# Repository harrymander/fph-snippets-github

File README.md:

# Code samples

1. `recap-instrumentation`: Research data collection device.

   C project for Atmel (Microchip) ATSAM4S16B using Freertos. Modules of
   interest:

   * `recap-instrumentation/sw/src/sensors.c`: sensor reading in timer ISR.
   * `recap-instrumentation/sw/drivers/twi-async/twi-async.c`: interrupt-driven
     'asynchronous' I2C read.

2. `recap-usb-reader`: Host application for the device above.

   Cross-platform C++ project for realtime data acquisition and visualisation.
   Uses Dear ImGui immediate mode GUI framework. GUI and application logic run
   from the event loop of graphics framework (DirectX on Windows, GLFW on
   Linux).

   Modules of interest:

   * `recap-usb-reader/gui/src/device.hpp`: boundary between the device library
     and the GUI. State pattern.
   * `recap-usb-reader/gui/src/observable.hpp`: observer pattern used to
     decouple the device layer from the GUI views.
   * `recap-usb-reader/lib/usb-reader/include/recap/usb-reader/reader.hpp`:
     device library interface.

3. `swallow-labeller`: Tool for annotating recordings from the device.
   (`complete-swallow-labelling` branch).

   C++, Dear ImGui. Modules of interest:

   * `swallow-labeller/src/gui/task-filter.cpp`: defining filters for different
     items in GUI list. Example of runtime polymorphism.
   * `swallow-labeller/src/gui/task-view.cpp`, lines 203-346: undo/redo using
     the command pattern.

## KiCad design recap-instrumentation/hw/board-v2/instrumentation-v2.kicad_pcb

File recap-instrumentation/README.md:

RECAP Instrumentation
=====================

Data collection device for the RECAP project. This is a reimplementation of the
original data collection prototype that was implemented using a Raspberry Pi.
This implementation is based around a Atmel SAM4S microcontroller connected to
the following sensors:

 - An ADC for audio recording
 - Air flow meter
 - Differential pressure sensor
 - H2S gas sensor

The data is continuously measured by the device and streamed over a USB CDC
interface using a custom data format. See [`sw/README.md`](sw/README.md) for
more information.

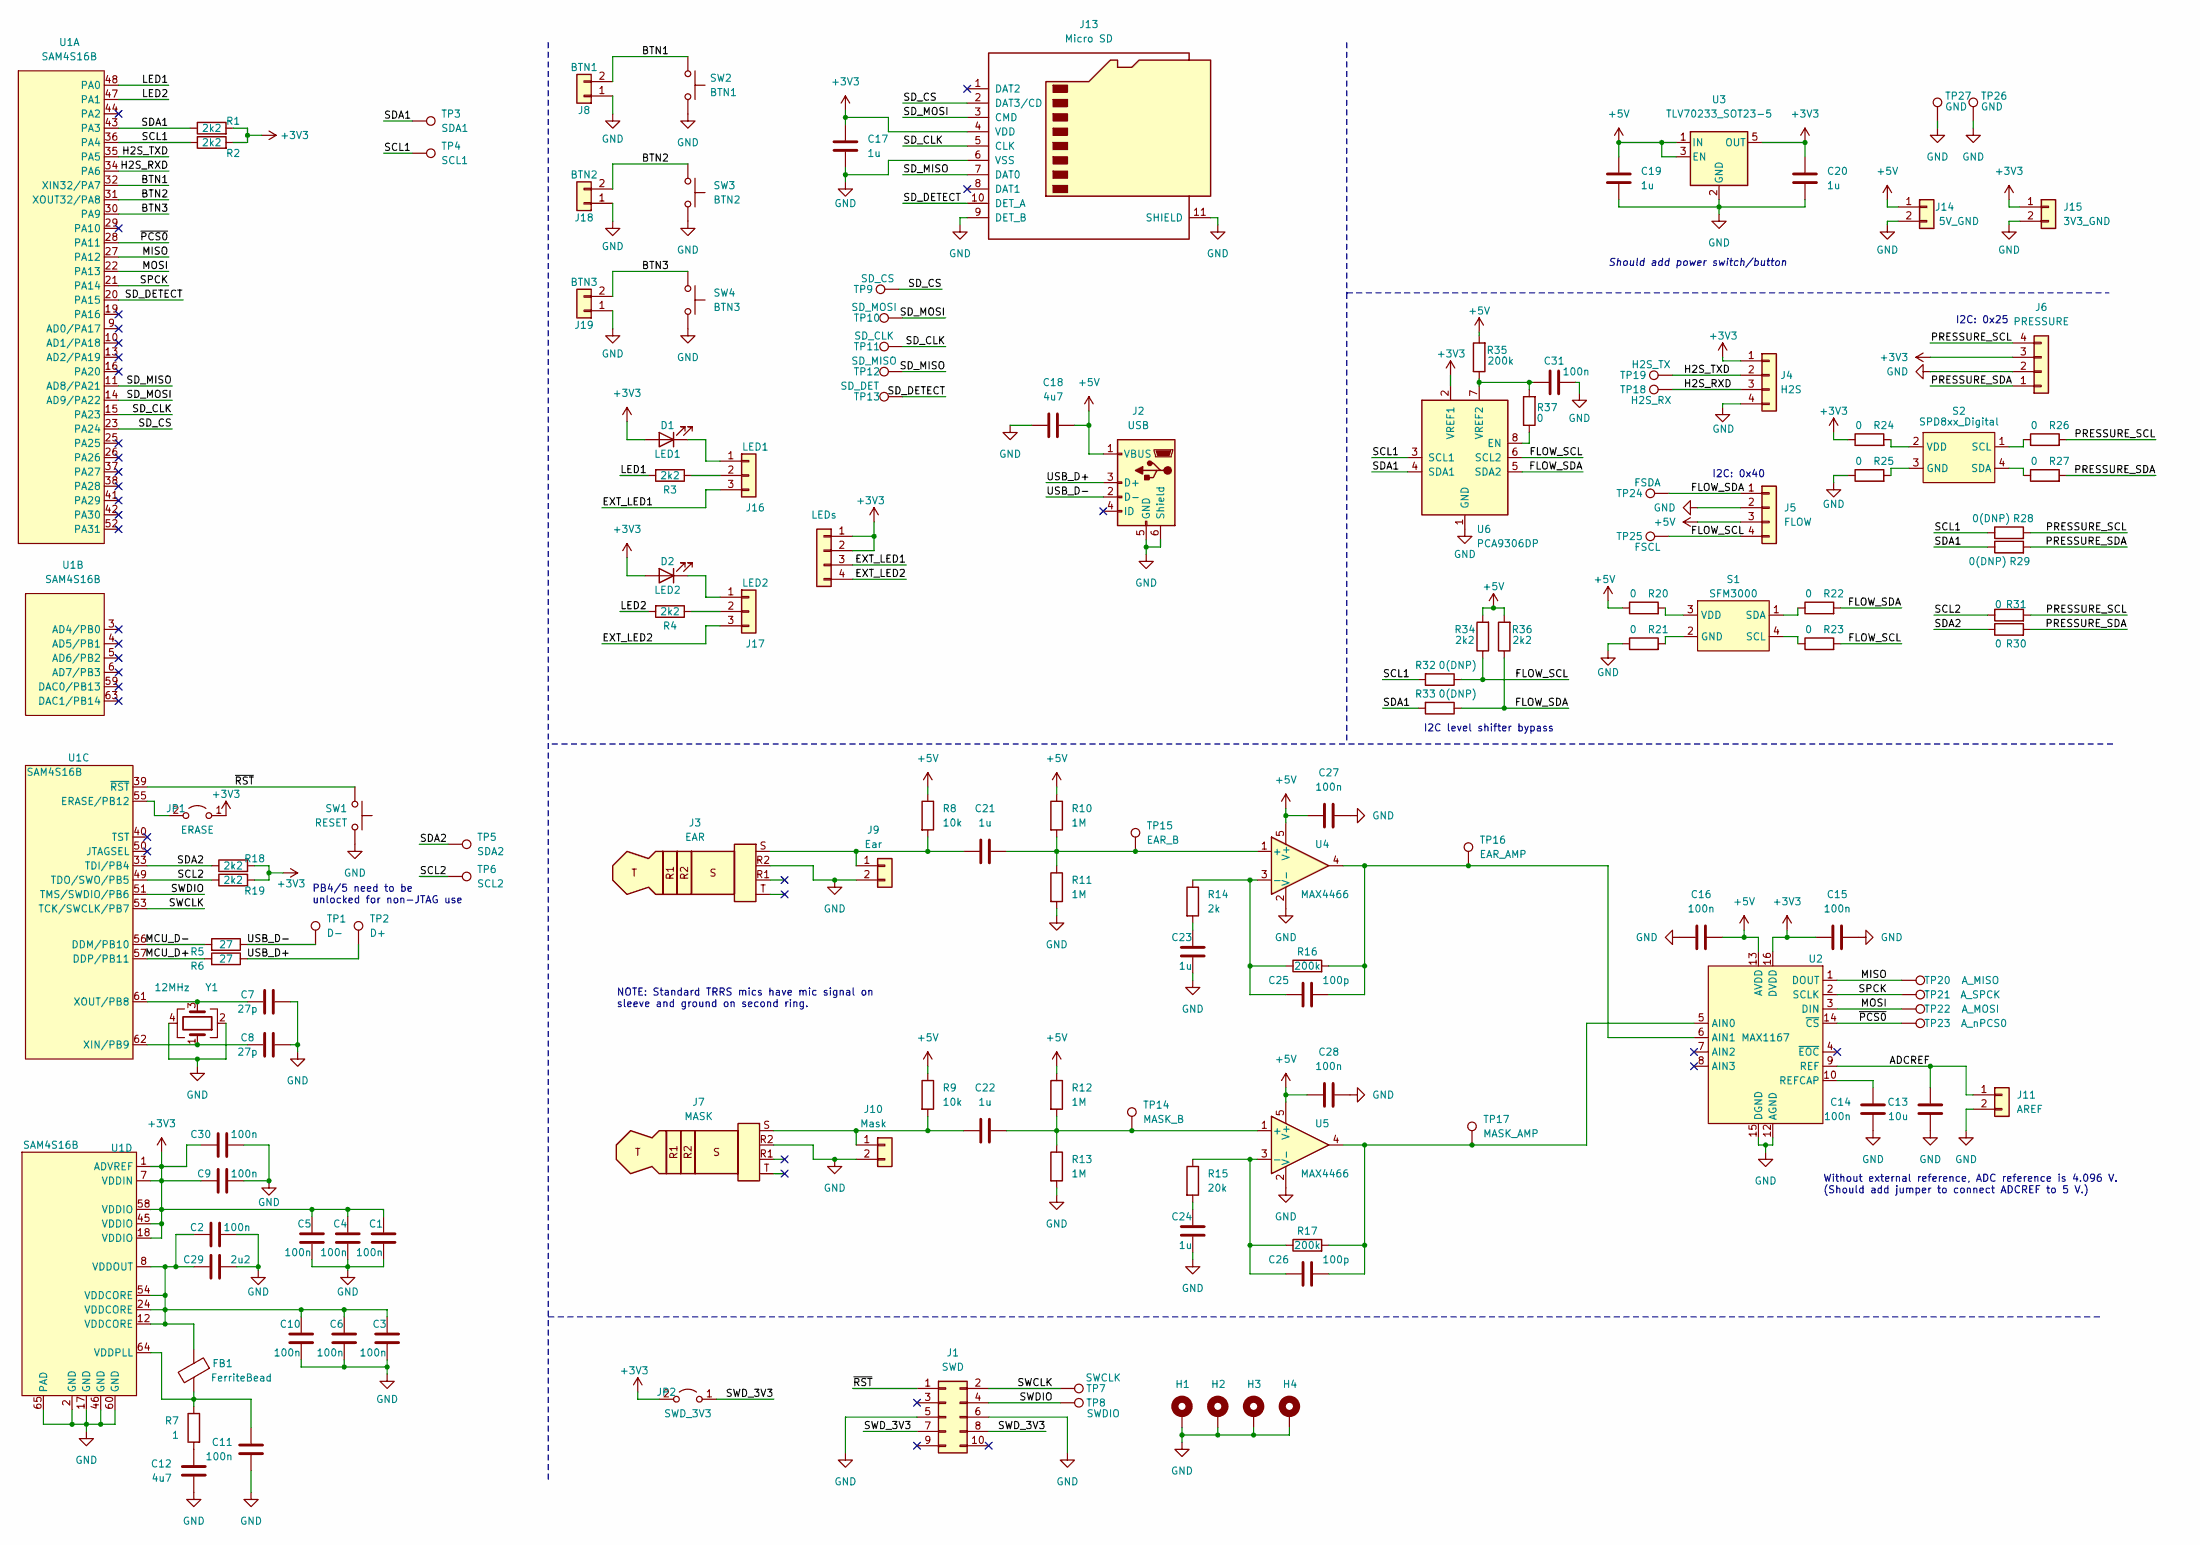
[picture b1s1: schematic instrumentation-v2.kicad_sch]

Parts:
C1, C2, C3, C4, C5, C6, C9, C10, C11, C14, C15, C16, C27, C28, C30, C31: 100n; C_0603_1608Metric
C7, C8: 27p; C_0603_1608Metric
C12, C18: 4u7; C_0603_1608Metric
C13: 10u; C_0805_2012Metric
C17, C19, C20: 1u; C_0603_1608Metric
C21, C22, C23, C24: 1u; C_Rect_L7.2mm_W4.5mm_P5.00mm_FKS2_FKP2_MKS2_MKP2
C25, C26: 100p; C_0603_1608Metric
C29: 2u2; C_0603_1608Metric
D1: LED1; LED_0603_1608Metric
D2: LED2; LED_0603_1608Metric
FB1: FerriteBead; L_0805_2012Metric
H1, H2, H3, H4: MountingHole_Pad; MountingHole_3.2mm_M3_Pad_Via
J1: SWD; IDC-Header_2x05_P2.54mm_Horizontal
J2: USB; USB_Micro-B_GCT_USB3076-30-A
J3: EAR; CUI_SJ-43514-SMT
J4: H2S; Molex_KK-254_AE-6410-04A_1x04_P2.54mm_Vertical
J5: FLOW; MOLEX_5600200420
J6: PRESSURE; MOLEX_5600200420
J7: MASK; CUI_SJ-43514-SMT
J8: BTN1; Molex_KK-254_AE-6410-02A_1x02_P2.54mm_Vertical
J9: Ear; PinHeader_1x02_P2.54mm_Vertical
J10: Mask; PinHeader_1x02_P2.54mm_Vertical
J11: AREF; PinHeader_1x02_P2.54mm_Vertical
J12: LEDs; Molex_KK-254_AE-6410-04A_1x04_P2.54mm_Vertical
J13: Micro SD; microSD_HC_Molex_104031-0811
J14: 5V_GND; PinHeader_1x02_P2.54mm_Vertical
J15: 3V3_GND; PinHeader_1x02_P2.54mm_Vertical
J16: LED1; PinHeader_1x03_P2.54mm_Vertical
J17: LED2; PinHeader_1x03_P2.54mm_Vertical
J18: BTN2; Molex_KK-254_AE-6410-02A_1x02_P2.54mm_Vertical
J19: BTN3; Molex_KK-254_AE-6410-02A_1x02_P2.54mm_Vertical
JP1: ERASE; PinHeader_1x02_P2.54mm_Vertical
JP2: SWD_3V3; PinHeader_1x02_P2.54mm_Vertical
R1, R2, R3, R4, R18, R19, R34, R36: 2k2; R_0603_1608Metric
R5, R6: 27; R_0603_1608Metric
R7: 1; R_0603_1608Metric
R8, R9: 10k; R_0603_1608Metric
R10, R11, R12, R13: 1M; R_0603_1608Metric
R14: 2k; R_0603_1608Metric
R15: 20k; R_0603_1608Metric
R16, R17, R35: 200k; R_0603_1608Metric
R20, R21, R22, R23, R24, R25, R26, R27, R30, R31, R37: 0; R_0603_1608Metric
R28, R29, R32, R33: 0(DNP); R_0603_1608Metric
S1: SFM3000
S2: SPD8xx_Digital; SPD8xx
SW1: RESET; SW_SPST_PTS645
SW2: BTN1; SW_SPST_PTS645
SW3: BTN2; SW_SPST_PTS645
SW4: BTN3; SW_SPST_PTS645
TP1: D-; TestPoint_Keystone_5019_Minature
TP2: D+; TestPoint_Keystone_5019_Minature
TP3: SDA1; TestPoint_Keystone_5019_Minature
TP4: SCL1; TestPoint_Keystone_5019_Minature
TP5: SDA2; TestPoint_Keystone_5019_Minature
TP6: SCL2; TestPoint_Keystone_5019_Minature
TP7: SWCLK; TestPoint_Keystone_5019_Minature
TP8: SWDIO; TestPoint_Keystone_5019_Minature
TP9: SD_CS; TestPoint_Keystone_5019_Minature
TP10: SD_MOSI; TestPoint_Keystone_5019_Minature
TP11: SD_CLK; TestPoint_Keystone_5019_Minature
TP12: SD_MISO; TestPoint_Keystone_5019_Minature
TP13: SD_DET; TestPoint_Keystone_5019_Minature
TP14: MASK_B; TestPoint_Keystone_5019_Minature
TP15: EAR_B; TestPoint_Keystone_5019_Minature
TP16: EAR_AMP; TestPoint_Keystone_5019_Minature
TP17: MASK_AMP; TestPoint_Keystone_5019_Minature
TP18: H2S_RX; TestPoint_Keystone_5019_Minature
TP19: H2S_TX; TestPoint_Keystone_5019_Minature
TP20: A_MISO; TestPoint_Keystone_5019_Minature
TP21: A_SPCK; TestPoint_Keystone_5019_Minature
TP22: A_MOSI; TestPoint_Keystone_5019_Minature
TP23: A_nPCS0; TestPoint_Keystone_5019_Minature
TP24: FSDA; TestPoint_Keystone_5019_Minature
TP25: FSCL; TestPoint_Keystone_5019_Minature
TP26, TP27: GND; TestPoint_Bridge_Pitch7.62mm_Drill1.3mm
U1: SAM4S16B; QFN-64-1EP_9x9mm_P0.5mm_EP7.3x7.3mm
U2: MAX1167; QSOP-16_3.9x4.9mm_P0.635mm
U3: TLV70233_SOT23-5; SOT-23-5
U4, U5: MAX4466; SOT-23-5
U6: PCA9306DP; TSSOP-8_3x3mm_P0.65mm
Y1: 12MHz; Crystal_SMD_0603-4Pin_6.0x3.5mm

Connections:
+3V3: C1.1, C4.1, C5.1, C9.1, C15.2, C17.1, C20.1, C30.1, D1.2 (A), D2.2 (A), J4.1, J6.3, J12.1, J12.2, J13.4 (VDD), J15.1, JP1.1 (A), JP2.2 (B), R1.2, R2.2, R18.2, R19.2, R24.1, U1.1 (ADVREF), U1.7 (VDDIN), U1.18 (VDDIO), U1.45 (VDDIO), U1.58 (VDDIO), U2.16 (DVDD), U3.5 (OUT), U6.2 (VREF1)
+5V: C16.1, C18.2, C19.1, C27.1, C28.1, J2.1 (VBUS), J5.3, J14.1, R8.1, R9.1, R10.1, R12.1, R20.1, R34.2, R35.2, R36.2, U2.13 (AVDD), U3.1 (IN), U3.3 (EN), U4.5 (V+), U5.5 (V+)
/ADCREF: C13.1, J11.1, U2.9 (REF)
/BTN1: J8.2, SW2.1, U1.32 (XIN32/PA7)
/BTN2: J18.2, SW3.1, U1.31 (XOUT32/PA8)
/BTN3: J19.2, SW4.1, U1.30 (PA9)
/EXT_LED1: J12.3, J16.3
/EXT_LED2: J12.4, J17.3
/FLOW_SCL: J5.4, R23.2, R32.1, R34.1, TP25.1, U6.6 (SCL2)
/FLOW_SDA: J5.1, R22.2, R33.1, R36.1, TP24.1, U6.5 (SDA2)
/H2S_RXD: J4.3, TP18.1, U1.34 (PA6)
/H2S_TXD: J4.2, TP19.1, U1.35 (PA5)
/LED1: R3.2, U1.48 (PA0)
/LED2: R4.2, U1.47 (PA1)
/MCU_D+: R6.2, U1.57 (DDP/PB11)
/MCU_D-: R5.2, U1.56 (DDM/PB10)
/MISO: TP20.1, U1.27 (PA12), U2.1 (DOUT)
/MOSI: TP22.1, U1.22 (PA13), U2.3 (DIN)
/PRESSURE_SCL: J6.4, R26.2, R28.2, R31.2
/PRESSURE_SDA: J6.1, R27.2, R29.2, R30.2
/SCL1: R2.1, R28.1, R32.2, TP4.1, U1.36 (PA4), U6.3 (SCL1)
/SCL2: R19.1, R31.1, TP6.1, U1.49 (TDO/SWO/PB5)
/SDA1: R1.1, R29.1, R33.2, TP3.1, U1.43 (PA3), U6.4 (SDA1)
/SDA2: R18.1, R30.1, TP5.1, U1.33 (TDI/PB4)
/SD_CLK: J13.5 (CLK), TP11.1, U1.15 (PA23)
/SD_CS: J13.2 (DAT3/CD), TP9.1, U1.23 (PA24)
/SD_DETECT: J13.10 (DET_A), TP13.1, U1.20 (PA15)
/SD_MISO: J13.7 (DAT0), TP12.1, U1.11 (AD8/PA21)
/SD_MOSI: J13.3 (CMD), TP10.1, U1.14 (AD9/PA22)
/SPCK: TP21.1, U1.21 (PA14), U2.2 (SCLK)
/SWCLK: J1.2, TP7.1, U1.53 (TCK/SWCLK/PB7)
/SWDIO: J1.4, TP8.1, U1.51 (TMS/SWDIO/PB6)
/SWD_3V3: J1.7, J1.8, JP2.1 (A)
/USB_D+: J2.3 (D+), R6.1, TP2.1
/USB_D-: J2.2 (D-), R5.1, TP1.1
/~PCS0: TP23.1, U1.28 (PA11), U2.14 (~CS)
/~RST: J1.1, SW1.2, U1.39 (~RST)
AGND: C1.2, C2.2, C3.2, C4.2, C5.2, C6.2, C7.1, C8.1, C9.2, C10.2, C11.2, C12.2, C13.2, C14.2, C15.1, C16.2, C17.2, C18.1, C19.2, C20.2, C23.2, C24.2, C27.2, C28.2, C29.2, C30.2, C31.2, H1.1, H2.1, H3.1, H4.1, J1.5, J1.6, J2.5 (GND), J2.6 (Shield), J3.R2, J4.4, J5.2, J6.2, J7.R2, J8.1, J9.2, J10.2, J11.2, J13.6 (VSS), J13.9 (DET_B), J13.11 (SHIELD), J14.2, J15.2, J18.1, J19.1, R11.2, R13.2, R21.1, R25.1, SW1.1, SW2.2, SW3.2, SW4.2, TP26.1, TP27.1, U1.2 (GND), U1.17 (GND), U1.46 (GND), U1.60 (GND), U1.65 (PAD), U2.11 (AGND), U2.12 (AGND), U2.15 (DGND), U3.2 (GND), U4.2 (V-), U5.2 (V-), U6.1 (GND), Y1.2, Y1.4
unnamed: C7.2, U1.61 (XOUT/PB8), Y1.3
unnamed: C8.2, U1.62 (XIN/PB9), Y1.1
unnamed: C2.1, C3.1, C6.1, C10.1, C29.1, FB1.1, U1.8 (VDDOUT), U1.12 (VDDCORE), U1.24 (VDDCORE), U1.54 (VDDCORE)
unnamed: C11.1, FB1.2, R7.1, U1.64 (VDDPLL)
unnamed: C12.1, R7.2
unnamed: C14.1, U2.10 (REFCAP)
unnamed: C21.1, J3.S, J9.1, R8.2
unnamed: C21.2, R10.2, R11.1, TP15.1, U4.1 (+)
unnamed: C22.1, J7.S, J10.1, R9.2
unnamed: C22.2, R12.2, R13.1, TP14.1, U5.1 (+)
unnamed: C23.1, R14.2
unnamed: C24.1, R15.2
unnamed: C25.1, R14.1, R16.1, U4.3 (-)
unnamed: C25.2, R16.2, TP16.1, U2.6 (AIN1), U4.4
unnamed: C26.1, R15.1, R17.1, U5.3 (-)
unnamed: C26.2, R17.2, TP17.1, U2.5 (AIN0), U5.4
unnamed: C31.1, R35.1, R37.2, U6.7 (VREF2)
unnamed: D1.1 (K), J16.1
unnamed: D2.1 (K), J17.1
unnamed: J16.2, R3.1
unnamed: J17.2, R4.1
unnamed: JP1.2 (B), U1.55 (ERASE/PB12)
unnamed: R20.2, S1.3 (VDD)
unnamed: R21.2, S1.2 (GND)
unnamed: R22.1, S1.1 (SDA)
unnamed: R23.1, S1.4 (SCL)
unnamed: R24.2, S2.2 (VDD)
unnamed: R25.2, S2.3 (GND)
unnamed: R26.1, S2.1 (SCL)
unnamed: R27.1, S2.4 (SDA)
unnamed: R37.1, U6.8 (EN)

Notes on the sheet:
Should add power switch/button
I2C: 0x25
I2C: 0x40
Without external reference, ADC reference is 4.096 V. (Should add jumper to connect ADCREF to 5 V.)
I2C level shifter bypass
PB4/5 need to be unlocked for non-JTAG use
NOTE: Standard TRRS mics have mic signal on sleeve and ground on second ring.

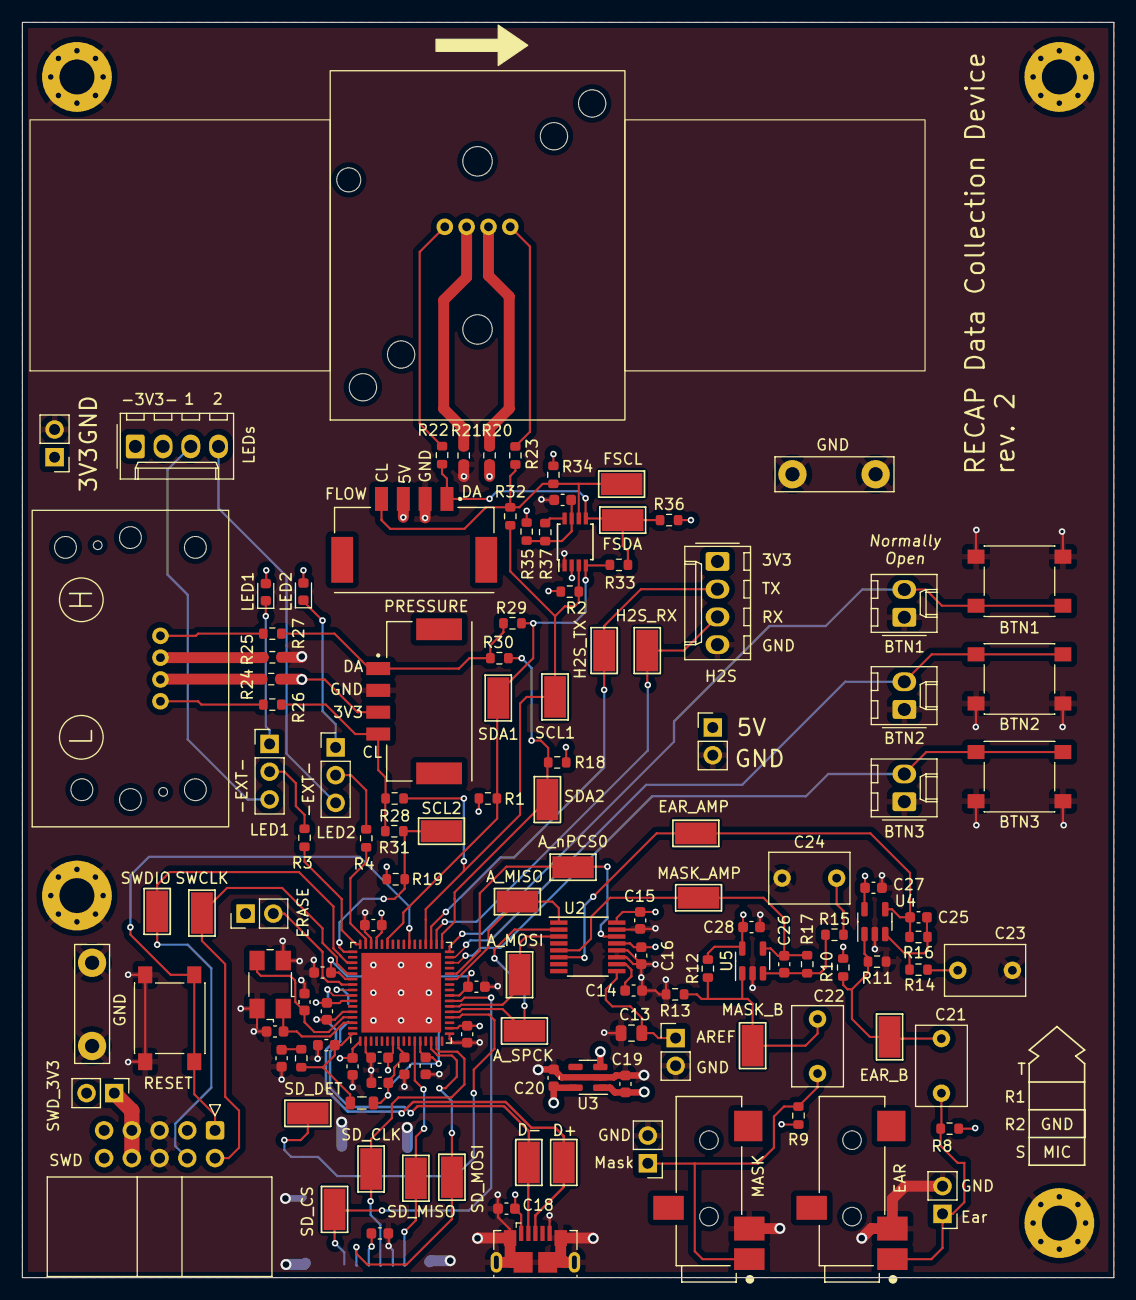
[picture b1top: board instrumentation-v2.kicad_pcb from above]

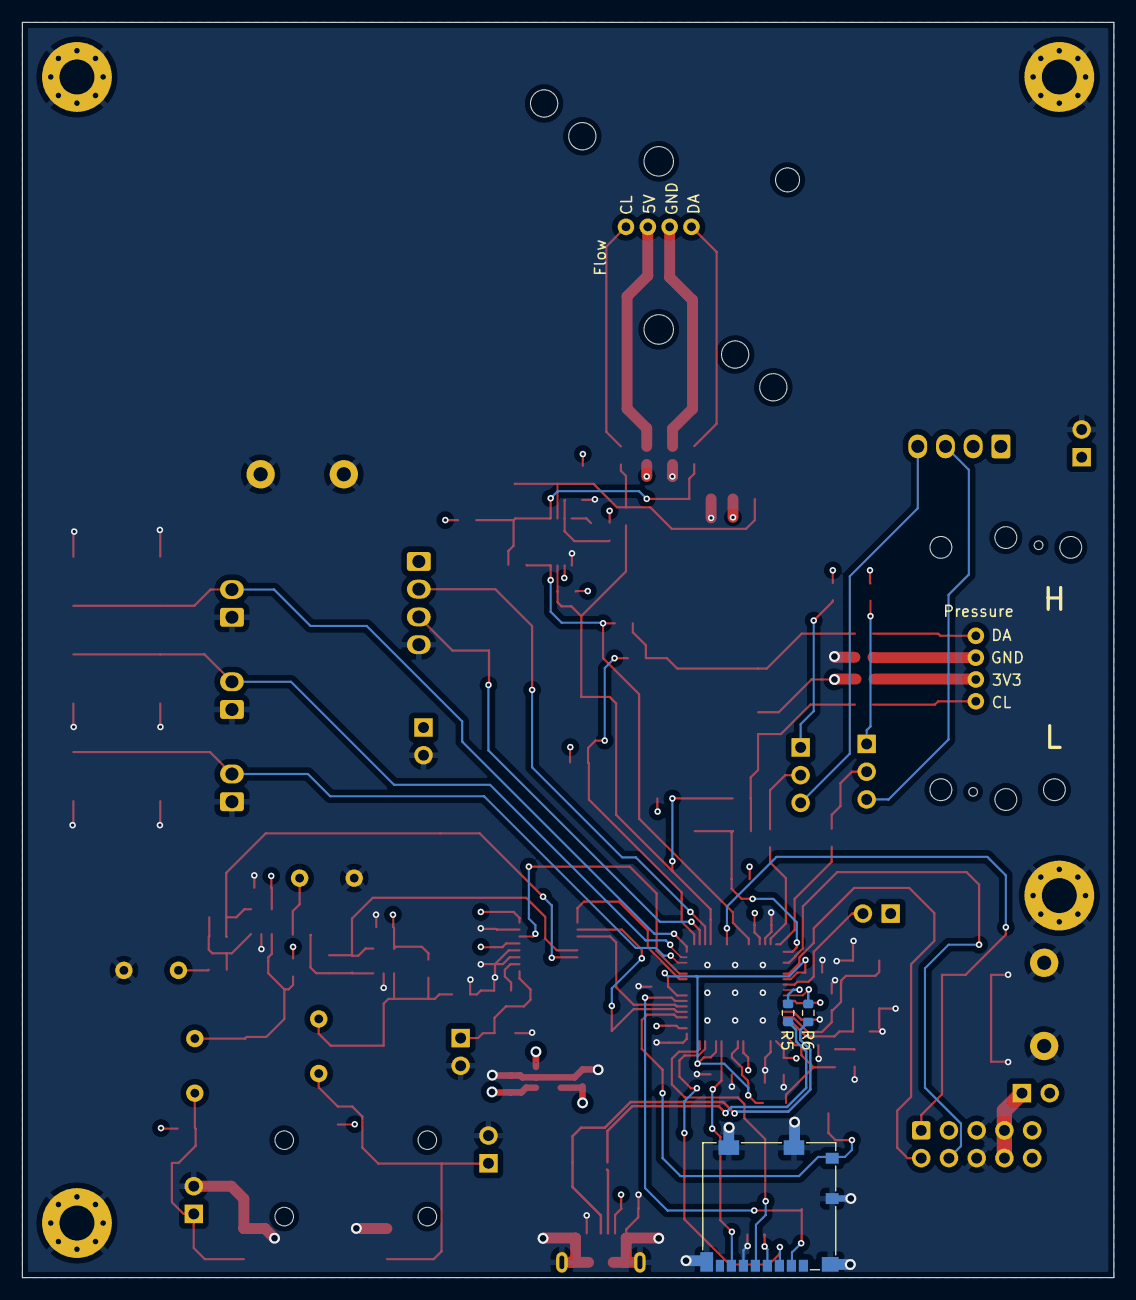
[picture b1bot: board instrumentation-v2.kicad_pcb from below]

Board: 4 copper layers, 100.0 x 115.0 mm, 136 parts (3 on the bottom side), 69 nets.

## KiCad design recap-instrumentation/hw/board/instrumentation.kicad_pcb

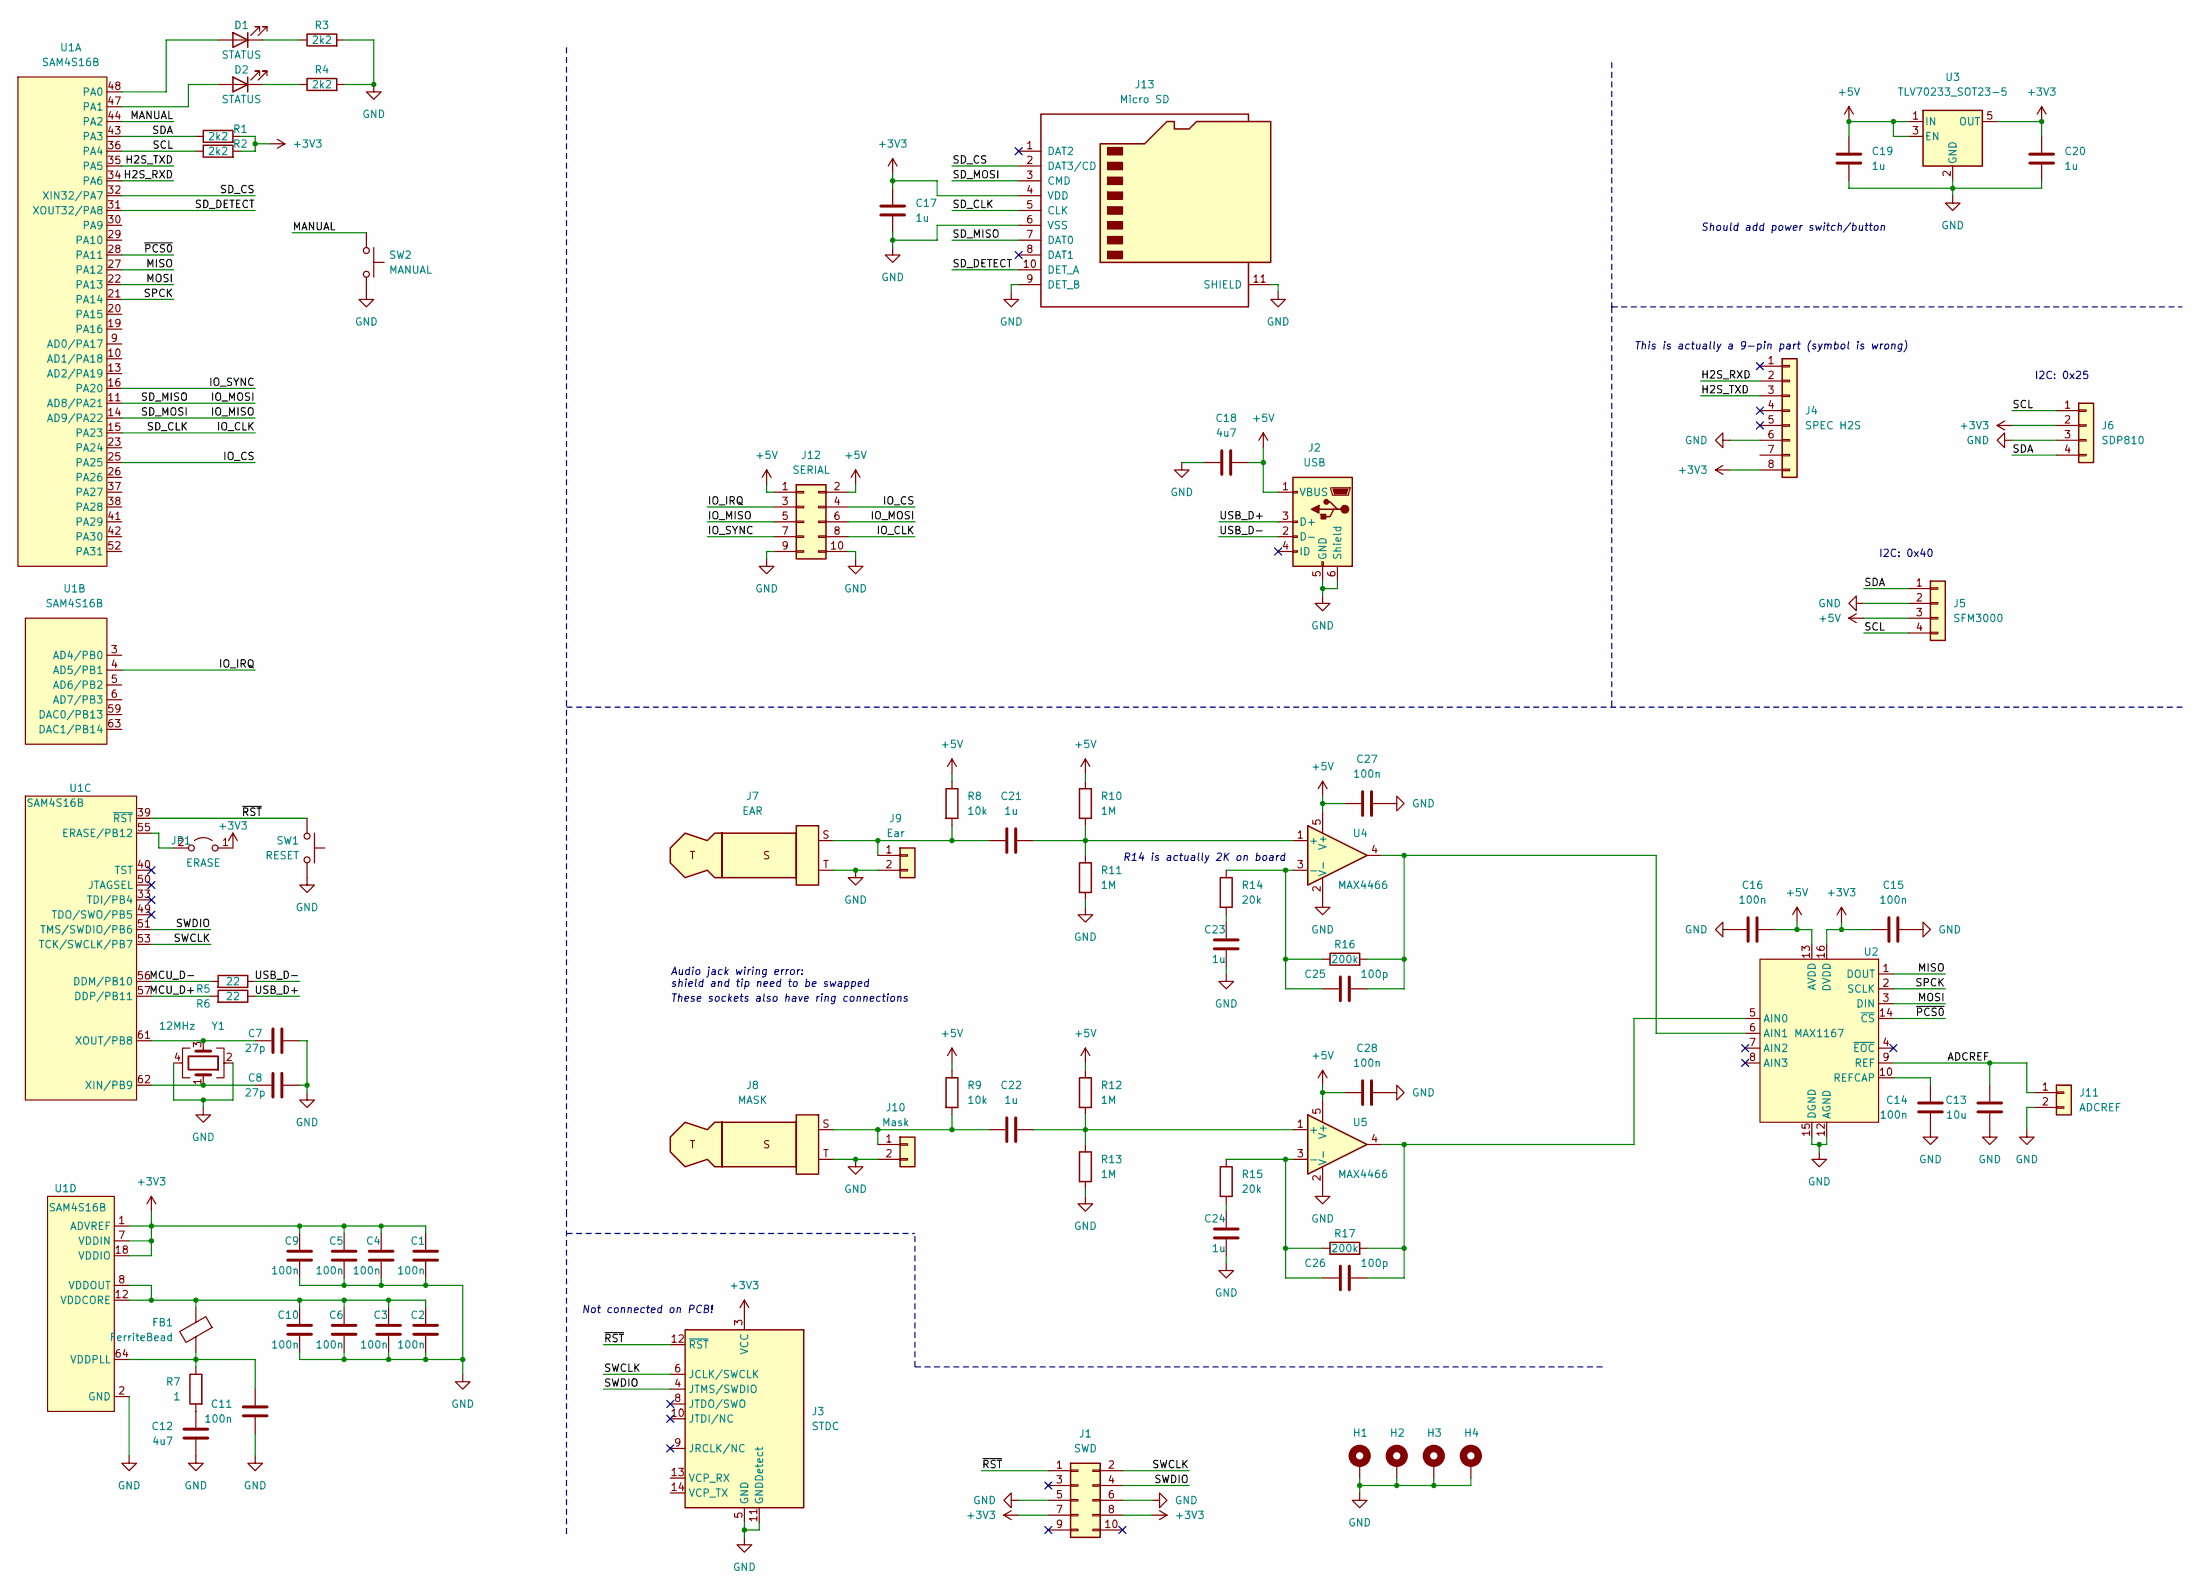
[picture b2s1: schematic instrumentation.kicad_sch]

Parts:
C1, C2, C3, C4, C5, C6, C9, C10, C11, C14, C15, C16, C27, C28: 100n; C_0603_1608Metric
C7, C8: 27p; C_0603_1608Metric
C12, C18: 4u7; C_0603_1608Metric
C13: 10u; C_0805_2012Metric
C17, C19, C20: 1u; C_0603_1608Metric
C21, C22, C23, C24: 1u; C_Rect_L7.2mm_W4.5mm_P5.00mm_FKS2_FKP2_MKS2_MKP2
C25, C26: 100p; C_0603_1608Metric
D1, D2: STATUS; LED_0603_1608Metric
FB1: FerriteBead; L_0805_2012Metric
H1, H2, H3, H4: MountingHole_Pad; MountingHole_3.2mm_M3_Pad_Via
J1: SWD; IDC-Header_2x05_P2.54mm_Vertical
J2: USB; USB_Micro-B_GCT_USB3076-30-A
J3: STDC; PinHeader_2x07_P1.27mm_Vertical_SMD
J4: SPEC H2S; PinHeader_1x09_P2.54mm_Vertical
J5: SFM3000; PinHeader_1x04_P2.00mm_Vertical
J6: SDP810; PinHeader_1x04_P2.00mm_Vertical
J7: EAR; Jack_3.5mm_CUI_SJ-3523-SMT_Horizontal
J8: MASK; Jack_3.5mm_CUI_SJ-3523-SMT_Horizontal
J9: Ear; PinHeader_1x02_P2.54mm_Vertical
J10: Mask; PinHeader_1x02_P2.54mm_Vertical
J11: ADCREF; PinHeader_1x02_P2.54mm_Vertical
J12: SERIAL; IDC-Header_2x05_P2.54mm_Vertical
J13: Micro SD; microSD_HC_Molex_104031-0811
JP1: ERASE; PinHeader_1x02_P2.54mm_Vertical
R1, R2, R3, R4: 2k2; R_0603_1608Metric
R5, R6: 22; R_0603_1608Metric
R7: 1; R_0603_1608Metric
R8, R9: 10k; R_0603_1608Metric
R10, R11, R12, R13: 1M; R_0603_1608Metric
R14, R15: 20k; R_0603_1608Metric
R16, R17: 200k; R_0603_1608Metric
SW1: RESET; SW_SPST_PTS645
SW2: MANUAL; SW_SPST_PTS645
U1: SAM4S16B; QFN-64-1EP_9x9mm_P0.5mm_EP7.3x7.3mm
U2: MAX1167; QSOP-16_3.9x4.9mm_P0.635mm
U3: TLV70233_SOT23-5; SOT-23-5
U4, U5: MAX4466; SOT-23-5
Y1: 12MHz; Crystal_SMD_0603-4Pin_6.0x3.5mm

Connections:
+3V3: C1.1, C4.1, C5.1, C9.1, C15.2, C17.1, C20.1, J1.7, J1.8, J3.3 (VCC), J4.8, J6.2, J13.4 (VDD), JP1.1 (A), R1.2, R2.2, U1.1 (ADVREF), U1.7 (VDDIN), U1.18 (VDDIO), U1.45 (VDDIO), U1.58 (VDDIO), U2.16 (DVDD), U3.5 (OUT)
+5V: C16.1, C18.2, C19.1, C27.1, C28.1, J2.1 (VBUS), J5.3, J12.1, J12.2, R8.1, R9.1, R10.1, R12.1, U2.13 (AVDD), U3.1 (IN), U3.3 (EN), U4.5 (V+), U5.5 (V+)
/ADCREF: C13.1, J11.1, U2.9 (REF)
/H2S_RXD: J4.2, U1.34 (PA6)
/H2S_TXD: J4.3, U1.35 (PA5)
/IO_CLK: J12.8, J13.5 (CLK), U1.15 (PA23)
/IO_CS: J12.4, U1.25 (PA25)
/IO_IRQ: J12.3, U1.4 (AD5/PB1)
/IO_MISO: J12.5, J13.3 (CMD), U1.14 (AD9/PA22)
/IO_MOSI: J12.6, J13.7 (DAT0), U1.11 (AD8/PA21)
/IO_SYNC: J12.7, U1.16 (PA20)
/MANUAL: SW2.1, U1.44 (PA2)
/MCU_D+: R6.2, U1.57 (DDP/PB11)
/MCU_D-: R5.2, U1.56 (DDM/PB10)
/MISO: U1.27 (PA12), U2.1 (DOUT)
/MOSI: U1.22 (PA13), U2.3 (DIN)
/SCL: J5.4, J6.1, R2.1, U1.36 (PA4)
/SDA: J5.1, J6.4, R1.1, U1.43 (PA3)
/SD_CS: J13.2 (DAT3/CD), U1.32 (XIN32/PA7)
/SD_DETECT: J13.10 (DET_A), U1.31 (XOUT32/PA8)
/SPCK: U1.21 (PA14), U2.2 (SCLK)
/SWCLK: J1.2, J3.6 (JCLK/SWCLK), U1.53 (TCK/SWCLK/PB7)
/SWDIO: J1.4, J3.4 (JTMS/SWDIO), U1.51 (TMS/SWDIO/PB6)
/USB_D+: J2.3 (D+), R6.1
/USB_D-: J2.2 (D-), R5.1
/~PCS0: U1.28 (PA11), U2.14 (~CS)
/~RST: J1.1, J3.12 (~RST), SW1.2, U1.39 (~RST)
AGND: C1.2, C2.2, C3.2, C4.2, C5.2, C6.2, C7.1, C8.1, C9.2, C10.2, C11.2, C12.2, C13.2, C14.2, C15.1, C16.2, C17.2, C18.1, C19.2, C20.2, C23.2, C24.2, C27.2, C28.2, H1.1, H2.1, H3.1, H4.1, J1.5, J1.6, J2.5 (GND), J2.6 (Shield), J3.5 (GND), J3.7 (GND), J3.11 (GNDDetect), J4.6, J5.2, J6.3, J7.T, J8.T, J9.2, J10.2, J11.2, J12.9, J12.10, J13.6 (VSS), J13.9 (DET_B), J13.11 (SHIELD), R3.2, R4.2, R11.2, R13.2, SW1.1, SW2.2, U1.2 (GND), U1.17 (GND), U1.46 (GND), U1.60 (GND), U2.11 (AGND), U2.12 (AGND), U2.15 (DGND), U3.2 (GND), U4.2 (V-), U5.2 (V-), Y1.2, Y1.4
unnamed: C7.2, U1.61 (XOUT/PB8), Y1.3
unnamed: C8.2, U1.62 (XIN/PB9), Y1.1
unnamed: C11.1, FB1.2, R7.1, U1.64 (VDDPLL)
unnamed: C12.1, R7.2
unnamed: C14.1, U2.10 (REFCAP)
unnamed: C21.1, J7.S, J9.1, R8.2
unnamed: C21.2, R10.2, R11.1, U4.1 (+)
unnamed: C22.1, J8.S, J10.1, R9.2
unnamed: C22.2, R12.2, R13.1, U5.1 (+)
unnamed: C23.1, R14.2
unnamed: C24.1, R15.2
unnamed: C25.1, R14.1, R16.1, U4.3 (-)
unnamed: C25.2, R16.2, U2.6 (AIN1), U4.4
unnamed: C26.1, R15.1, R17.1, U5.3 (-)
unnamed: C26.2, R17.2, U2.5 (AIN0), U5.4
unnamed: D1.1 (K), R3.1
unnamed: D1.2 (A), U1.48 (PA0)
unnamed: D2.1 (K), R4.1
unnamed: D2.2 (A), U1.47 (PA1)
unnamed: JP1.2 (B), U1.55 (ERASE/PB12)
VDDCORE: C2.1, C3.1, C6.1, C10.1, FB1.1, U1.8 (VDDOUT), U1.12 (VDDCORE), U1.24 (VDDCORE), U1.54 (VDDCORE)

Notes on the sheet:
Should add power switch/button
These sockets also have ring connections
I2C: 0x25
I2C: 0x40
This is actually a 9-pin part (symbol is wrong)
R14 is actually 2K on board
Not connected on PCB!
Audio jack wiring error: shield and tip need to be swapped

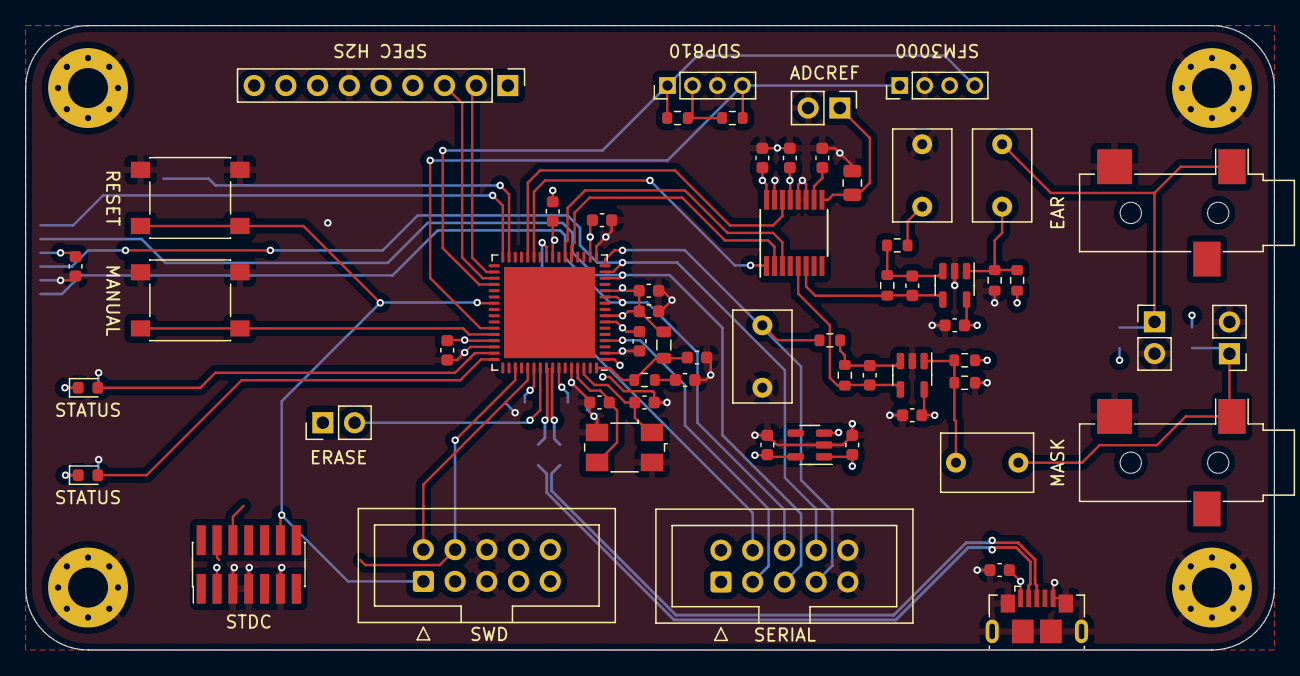
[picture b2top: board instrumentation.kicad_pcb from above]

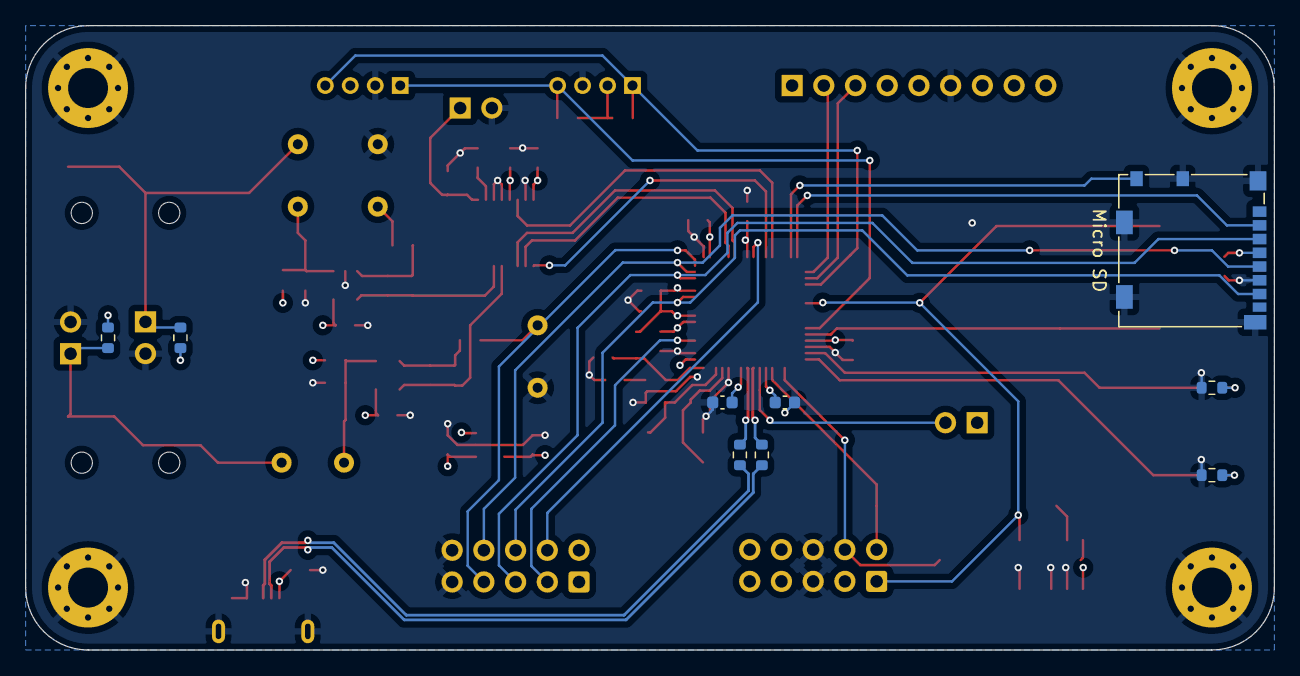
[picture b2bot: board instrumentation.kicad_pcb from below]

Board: 4 copper layers, 100.0 x 50.0 mm, 74 parts (9 on the bottom side), 49 nets.

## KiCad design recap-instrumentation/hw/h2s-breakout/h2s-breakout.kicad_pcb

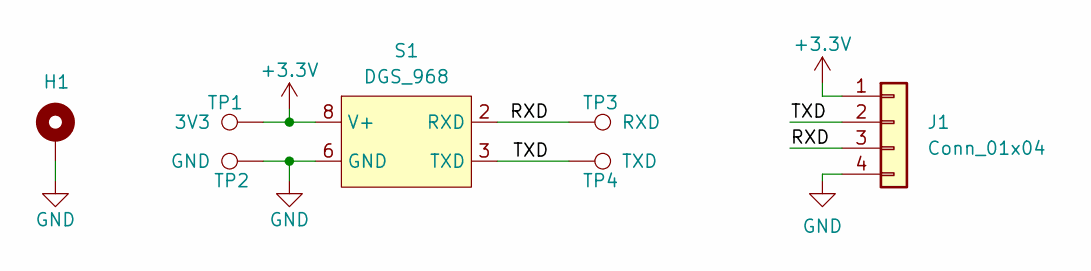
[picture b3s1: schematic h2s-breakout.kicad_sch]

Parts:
H1: MountingHole_Pad; MountingHole_3.2mm_M3_Pad_Via
J1: Conn_01x04; Molex_KK-254_1x04_P2.54mm_Horizontal
S1: DGS_968
TP1: 3V3; TestPoint_Keystone_5019_Minature
TP2: GND; TestPoint_Keystone_5019_Minature
TP3: RXD; TestPoint_Keystone_5019_Minature
TP4: TXD; TestPoint_Keystone_5019_Minature

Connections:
+3.3V: J1.1, S1.8 (V+), TP1.1
/RXD: J1.3, S1.2 (RXD), TP3.1
/TXD: J1.2, S1.3 (TXD), TP4.1
GND: H1.1, J1.4, S1.6 (GND), TP2.1

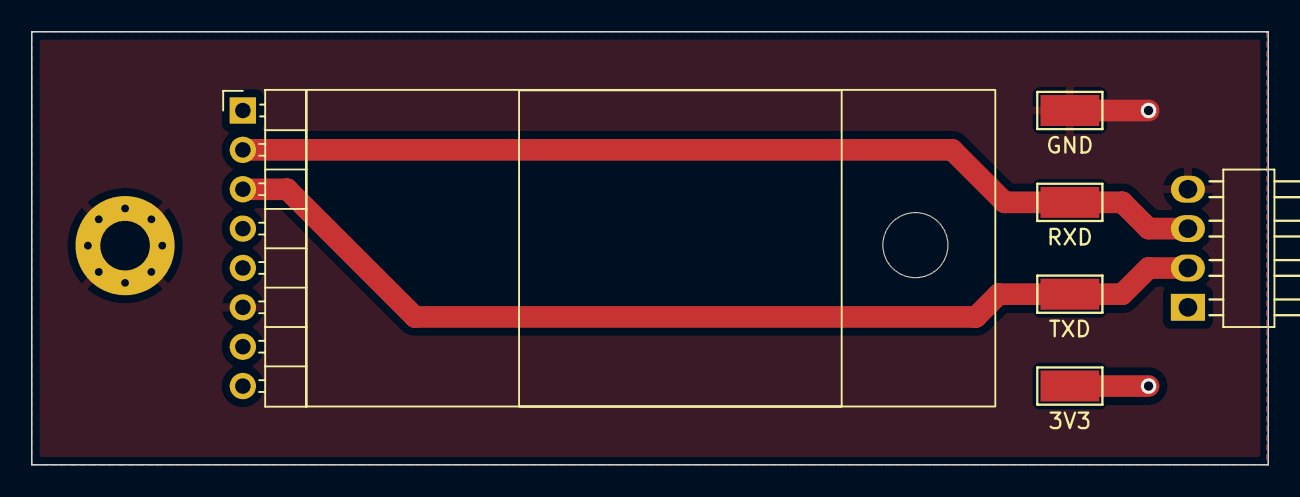
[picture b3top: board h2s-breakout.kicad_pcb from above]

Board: 4 copper layers, 79.8 x 27.9 mm, 7 parts (0 on the bottom side), 4 nets.
